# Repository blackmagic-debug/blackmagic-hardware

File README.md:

This project has now moved to [codeberg](https://codeberg.org/blackmagic-debug/blackmagic-hardware). Please file any issues and pull
requests there.

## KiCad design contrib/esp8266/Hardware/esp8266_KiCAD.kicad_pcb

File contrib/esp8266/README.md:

ESP8266 Clone
========================================

A little adapter board for connecting ESP-01 module as a debugger.

Repository Contents
-------------------

* **/Production** - Gerber files, drill files, BOM, CPL file
* **/Hardware** - KiCad PCB files, footprints library
* **/Documents** - Schematics pdf

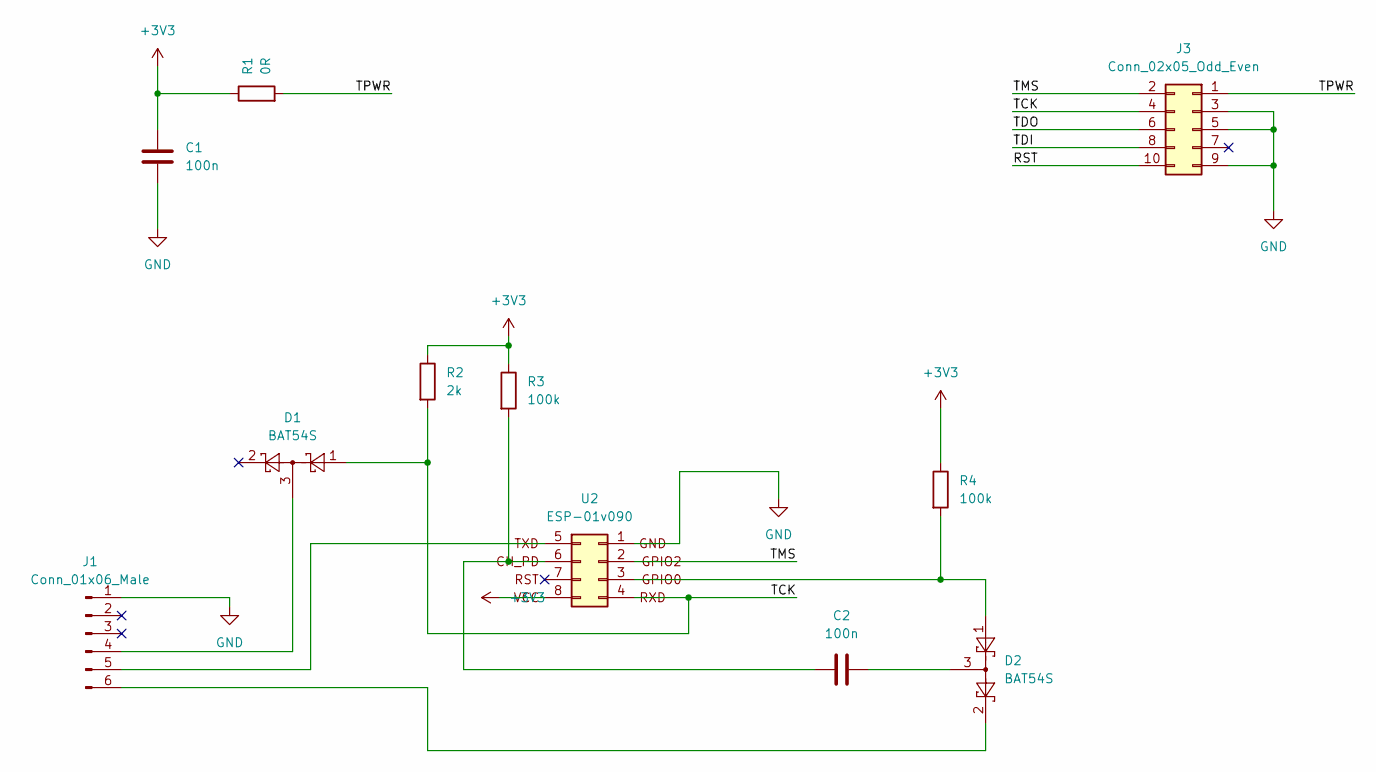
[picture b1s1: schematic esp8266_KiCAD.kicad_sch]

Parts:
C1, C2: 100n; C_0402_1005Metric; LCSC Number Part C1525
D1, D2: BAT54S; SOT-23; LCSC Number Part C727126
J1: Conn_01x06_Male; PinHeader_1x06_P2.54mm_Vertical
J3: Conn_02x05_Odd_Even; FTSH; LCSC Number Part C2935458
R1: 0R; R_0402_1005Metric; LCSC Number Part C17168
R2: 2k; R_0402_1005Metric; LCSC Number Part C4109
R3, R4: 100k; R_0402_1005Metric; LCSC Number Part C25741
U2: ESP-01v090; ESP-01S; LCSC Number Part C503582

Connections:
+3V3: C1.1, R1.1, R2.1, R3.1, R4.1, U2.8 (Pin_7)
/RST: J3.10
/TCK: D1.1, J3.4, R2.2, U2.4 (Pin_8)
/TDI: J3.8
/TDO: J3.6
/TMS: J3.2, U2.2 (Pin_4)
/TPWR: J3.1, R1.2
GND: C1.2, J1.1, J3.3, J3.5, J3.9, U2.1 (Pin_2)
unnamed: C2.1, R3.2, U2.6 (Pin_3)
unnamed: C2.2, D2.3
unnamed: D1.3, J1.4
unnamed: D2.1, R4.2, U2.3 (Pin_6)
unnamed: D2.2, J1.6
unnamed: J1.5, U2.5 (Pin_1)

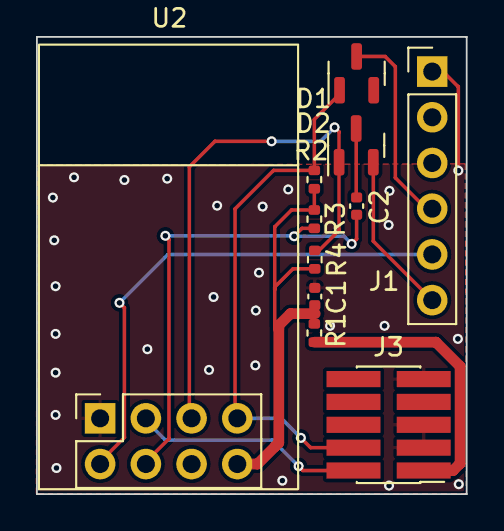
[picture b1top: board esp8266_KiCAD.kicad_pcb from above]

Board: 2 copper layers, 23.9 x 25.4 mm, 11 parts (0 on the bottom side), 11 nets.

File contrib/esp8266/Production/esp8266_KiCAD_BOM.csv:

"Source:","C:\Users\Sergio\Documents\EOS\esp8266\esp8266_KiCAD\esp8266_KiCAD\esp8266_KiCAD.kicad_sch"
"Date:","08/09/2022 10:14:48"
"Tool:","Eeschema (6.0.7)"
"Generator:","C:\Program Files\KiCad\6.0\bin\scripting\plugins/bom_csv_grouped_by_value.py"
"Component Count:","10"

"Individual Components:"

"Item","Qty","Reference(s)","Value","LibPart","Footprint","Datasheet","LCSC Number Part"
"","","C1","100n","Device:C","Capacitor_SMD:C_0402_1005Metric","~","C1525"
"","","C2","100n","Device:C","Capacitor_SMD:C_0402_1005Metric","~","C1525"
"","","D1","BAT54S","Diode:BAT54S","Package_TO_SOT_SMD:SOT-23","https://www.diodes.com/assets/Datasheets/ds11005.pdf","C727126"
"","","D2","BAT54S","Diode:BAT54S","Package_TO_SOT_SMD:SOT-23","https://www.diodes.com/assets/Datasheets/ds11005.pdf","C727126"
"","","J3","Conn_02x05_Odd_Even","Connector_Generic:Conn_02x05_Odd_Even","EOS:FTSH","~","C2935458"
"","","R1","0R","Device:R","Resistor_SMD:R_0402_1005Metric","~","C17168"
"","","R2","2k","Device:R","Resistor_SMD:R_0402_1005Metric","~","C4109"
"","","R3","100k","Device:R","Resistor_SMD:R_0402_1005Metric","~","C25741"
"","","R4","100k","Device:R","Resistor_SMD:R_0402_1005Metric","~","C25741"
"","","U2","ESP-01v090","Connector_Generic:Conn_02x04_Odd_Even","EOS:ESP-01S","~","C503582"

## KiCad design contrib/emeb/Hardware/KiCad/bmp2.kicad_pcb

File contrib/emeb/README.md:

Black Magic BMP2 Clone
========================================

Black Magic BMP2 is similar to Black Magic Mini but provides connections for several styles of JTAG connectors.

It is an easy-to-use board used for debugging embedded microcontrollers. It supports several targets from manufacturers such as STMicroelectronics, Atmel, Nordic Semiconductor, NXP, Texas Instruments, Freescale, Silicon Labs, Xilinx or Raspberry Pi.

GNU debugger
-------------------
The Black Magic GNU DeBugger (GDB) server features:
* Automatic target detection
* No need for target specific configuration scripts
* Easily scriptable
* Interface to the host computer does not require special drivers
* Full debugging functionality
* Works with Windows, Linux and Mac environments

Repository Contents
-------------------

* **/Production** - Gerber files, drill files, BOM, CPL file
* **/Hardware** - KiCad PCB files, footprints library
* **/Documents** - Schematics pdf

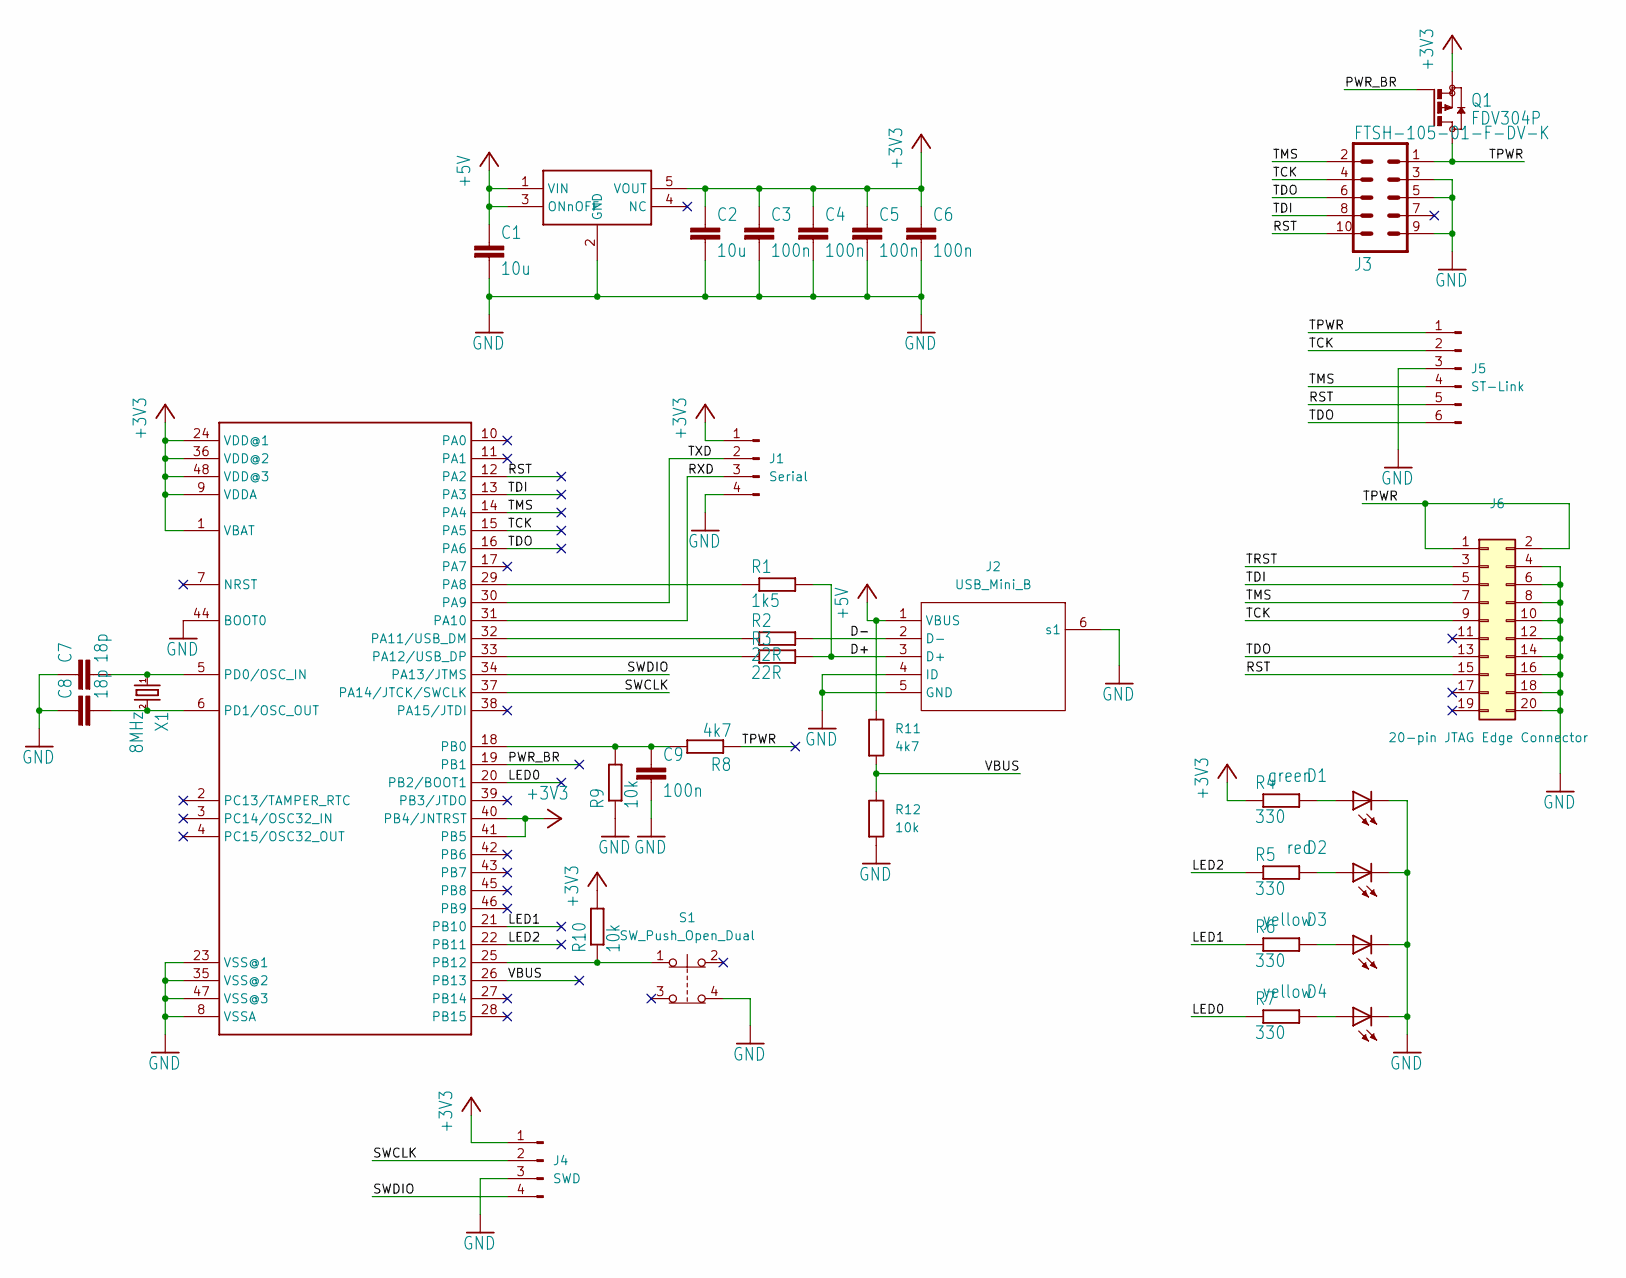
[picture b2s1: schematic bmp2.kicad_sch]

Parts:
C1, C2: 10u; C_0805_2012Metric; LCSC Number Part C17024
C3, C4, C5, C6, C9: 100n; C_0603_1608Metric; LCSC Number Part C1591
C7, C8: 18p; C_0603_1608Metric; LCSC Number Part C1647
D1: green; LED_0805_2012Metric; LCSC Number Part C434432
D2: red; LED_0805_2012Metric; LCSC Number Part C434431
D3, D4: yellow; LED_0805_2012Metric; LCSC Number Part C434436
J1: Serial; PinHeader_1x04_P2.54mm_Vertical
J2: USB_Mini_B; U-M-M5SS-W-2; LCSC Number Part C91144
J3: FTSH-105-01-F-DV-K; X1270WVS-2x05A-6TV01; LCSC Number Part C2962222
J4: SWD; PinHeader_1x04_P2.54mm_Vertical
J5: ST-Link; PinHeader_1x06_P2.54mm_Vertical
J6: 20-pin JTAG Edge Connector; 20-pin JTAG
Q1: FDV304P; SOT-23; LCSC Number Part C709971
R1: 1k5; R_0603_1608Metric; LCSC Number Part C22843
R2, R3: 22R; R_0603_1608Metric; LCSC Number Part C23345
R4, R5, R6, R7: 330; R_0603_1608Metric; LCSC Number Part C23138
R8, R11: 4k7; R_0603_1608Metric; LCSC Number Part C23162
R9, R10, R12: 10k; R_0603_1608Metric; LCSC Number Part C25804
S1: SW_Push_Open_Dual; UK-B0267-SP25Y; LCSC Number Part C493283
U1: MCP1802; SOT-23-5; LCSC Number Part C48292
U2: STM32F102CB; TQFP48; LCSC Number Part C8304
X1: 8MHz; 6I08000F20UCG; LCSC Number Part C251585

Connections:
+3V3: C2.1, C3.1, C4.1, C5.1, C6.1, J1.1, J4.1, Q1.2 (S), R4.1, R10.2, U1.5 (VOUT), U2.1 (VBAT), U2.9 (VDDA), U2.24 (VDD@1), U2.36 (VDD@2), U2.40 (PB4/JNTRST), U2.41 (PB5), U2.48 (VDD@3)
+5V: C1.1, J2.1 (VBUS), R11.1, U1.1 (VIN), U1.3 (ONnOFF)
/D+: J2.3 (D+), R1.2, R3.2
/D-: J2.2 (D-), R2.2
/LED0: R7.1, U2.20 (PB2/BOOT1)
/LED1: R6.1, U2.21 (PB10)
/LED2: R5.1, U2.22 (PB11)
/PWR_BR: Q1.1 (G), U2.19 (PB1)
/RST: J3.10, J5.5, J6.15, U2.12 (PA2)
/RXD: J1.3, U2.31 (PA10)
/SWCLK: J4.2, U2.37 (PA14/JTCK/SWCLK)
/SWDIO: J4.4, U2.34 (PA13/JTMS)
/TCK: J3.4, J5.2, J6.9, U2.15 (PA5)
/TDI: J3.8, J6.5, U2.13 (PA3)
/TDO: J3.6, J5.6, J6.13, U2.16 (PA6)
/TMS: J3.2, J5.4, J6.7, U2.14 (PA4)
/TPWR: J3.1, J5.1, J6.1, J6.2, Q1.3 (D), R8.1
/TRST: J6.3
/TXD: J1.2, U2.30 (PA9)
/VBUS: R11.2, R12.1, U2.26 (PB13)
GND: C1.2, C2.2, C3.2, C4.2, C5.2, C6.2, C7.1, C8.1, C9.2, D1.2 (C), D2.2 (C), D3.2 (C), D4.2 (C), J1.4, J2.4 (ID), J2.5 (GND), J2.6 (s1), J3.3, J3.5, J3.9, J4.3, J5.3, J6.4, J6.6, J6.8, J6.10, J6.12, J6.14, J6.16, J6.18, J6.20, R9.1, R12.2, S1.4, U1.2 (GND), U2.8 (VSSA), U2.23 (VSS@1), U2.35 (VSS@2), U2.44 (BOOT0), U2.47 (VSS@3)
unnamed: C7.2, U2.5 (PD0/OSC_IN), X1.1
unnamed: C8.2, U2.6 (PD1/OSC_OUT), X1.2
unnamed: C9.1, R8.2, R9.2, U2.18 (PB0)
unnamed: D1.1 (A), R4.2
unnamed: D2.1 (A), R5.2
unnamed: D3.1 (A), R6.2
unnamed: D4.1 (A), R7.2
unnamed: R1.1, U2.29 (PA8)
unnamed: R2.1, U2.32 (PA11/USB_DM)
unnamed: R3.1, U2.33 (PA12/USB_DP)
unnamed: R10.1, S1.1, U2.25 (PB12)

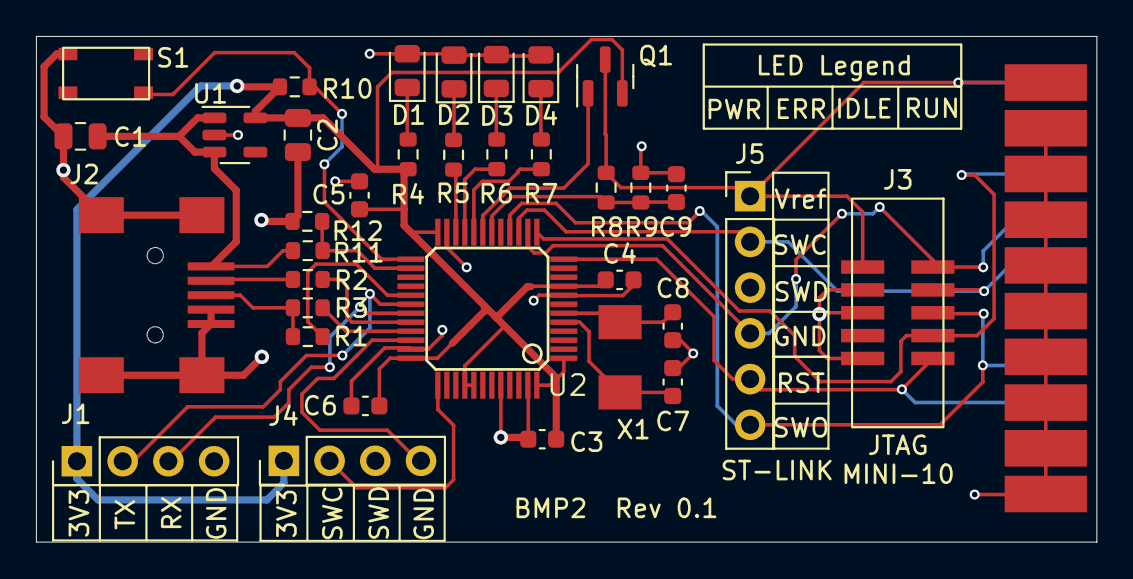
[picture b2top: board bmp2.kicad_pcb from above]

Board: 2 copper layers, 58.9 x 28.1 mm, 36 parts (0 on the bottom side), 31 nets.

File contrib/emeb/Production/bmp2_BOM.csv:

"Source:","C:\Users\Sergio\Documents\EOS\blackmagic-hardware-master\contrib\bmp2\bmp2_KiCAD\bmp2_KiCAD\bmp2.kicad_sch"
"Date:","01/09/2022 12:01:49"
"Tool:","Eeschema (6.0.7)"
"Generator:","C:\Program Files\KiCad\6.0\bin\scripting\plugins/bom_csv_grouped_by_value.py"
"Component Count:","32"

"Individual Components:"

"Item","Qty","Reference(s)","Value","LibPart","Footprint","Datasheet","LCSC Number Part"
"","","C1","10u","bmp_entropia-eagle-import:C-EUC0603","Capacitor_SMD:C_0805_2012Metric","","C17024"
"","","C2","10u","bmp_entropia-eagle-import:C-EUC0603","Capacitor_SMD:C_0805_2012Metric","","C17024"
"","","C3","100n","bmp_entropia-eagle-import:C-EUC0603","Capacitor_SMD:C_0603_1608Metric","","C1591"
"","","C4","100n","bmp_entropia-eagle-import:C-EUC0603","Capacitor_SMD:C_0603_1608Metric","","C1591"
"","","C5","100n","bmp_entropia-eagle-import:C-EUC0603","Capacitor_SMD:C_0603_1608Metric","","C1591"
"","","C6","100n","bmp_entropia-eagle-import:C-EUC0603","Capacitor_SMD:C_0603_1608Metric","","C1591"
"","","C7","18p","bmp_entropia-eagle-import:C-EUC0603","Capacitor_SMD:C_0603_1608Metric","","C1647"
"","","C8","18p","bmp_entropia-eagle-import:C-EUC0603","Capacitor_SMD:C_0603_1608Metric","","C1647"
"","","C9","100n","bmp_entropia-eagle-import:C-EUC0603","Capacitor_SMD:C_0603_1608Metric","","C1591"
"","","D1","green",":LEDCHIPLED_0603_1","LED_SMD:LED_0805_2012Metric","","C434432"
"","","D2","red",":LEDCHIPLED_0603_2","LED_SMD:LED_0805_2012Metric","","C434431"
"","","D3","yellow",":LEDCHIPLED_0603_3","LED_SMD:LED_0805_2012Metric","","C434436"
"","","D4","yellow","bmp_entropia-eagle-import:LEDCHIPLED_0603","LED_SMD:LED_0805_2012Metric","","C434436"
"","","J2","USB_Mini_B","BMP2:USB_Mini_B","EOS:U-M-M5SS-W-2","","C91144"
"","","J3","FTSH-105-01-F-DV-K","bmp_entropia-eagle-import:MA05-2","EOS:X1270WVS-2x05A-6TV01","","C2962222"
"","","Q1","FDV304P","bmp_entropia-eagle-import:BSS84","Package_TO_SOT_SMD:SOT-23","","C709971"
"","","R1","1k5","bmp_entropia-eagle-import:R-EU_R0603","Resistor_SMD:R_0603_1608Metric","","C22843"
"","","R2","22R","bmp_entropia-eagle-import:R-EU_R0603","Resistor_SMD:R_0603_1608Metric","","C23345"
"","","R3","22R","bmp_entropia-eagle-import:R-EU_R0603","Resistor_SMD:R_0603_1608Metric","","C23345"
"","","R4","330","bmp_entropia-eagle-import:R-EU_R0603","Resistor_SMD:R_0603_1608Metric","","C23138"
"","","R5","330","bmp_entropia-eagle-import:R-EU_R0603","Resistor_SMD:R_0603_1608Metric","","C23138"
"","","R6","330","bmp_entropia-eagle-import:R-EU_R0603","Resistor_SMD:R_0603_1608Metric","","C23138"
"","","R7","330","bmp_entropia-eagle-import:R-EU_R0603","Resistor_SMD:R_0603_1608Metric","","C23138"
"","","R8","4k7","bmp_entropia-eagle-import:R-EU_R0603","Resistor_SMD:R_0603_1608Metric","","C23162"
"","","R9","10k","bmp_entropia-eagle-import:R-EU_R0603","Resistor_SMD:R_0603_1608Metric","","C25804"
"","","R10","10k","bmp_entropia-eagle-import:R-EU_R0603","Resistor_SMD:R_0603_1608Metric","","C25804"
"","","R11","4k7","Device:R","Resistor_SMD:R_0603_1608Metric","~","C23162"
"","","R12","10k","Device:R","Resistor_SMD:R_0603_1608Metric","~","C25804"
"","","S1","SW_Push_Open_Dual","Switch:SW_Push_Open_Dual","EOS:UK-B0267-SP25Y","~","C493283"
"","","U1","MCP1802","bmp_entropia-eagle-import:TLV700DCK","Package_TO_SOT_SMD:SOT-23-5","","C48292"
"","","U2","STM32F102CB","bmp_entropia-eagle-import:STM32F_48PIN","bmp_entropia:TQFP48","","C8304"
"","","X1","8MHz","bmp_entropia-eagle-import:CRYSTALHC49S","EOS:6I08000F20UCG","","C251585"

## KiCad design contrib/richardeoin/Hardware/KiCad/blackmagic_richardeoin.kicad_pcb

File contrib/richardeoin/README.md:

Black Magic Richardeoin Clone
========================================

Black Magic Richardeoin is version of Black Magic Mini with some differences such as the useage of 0603 components or a BOOT0 button.

It is an easy-to-use board used for debugging embedded microcontrollers. It supports several targets from manufacturers such as STMicroelectronics, Atmel, Nordic Semiconductor, NXP, Texas Instruments, Freescale, Silicon Labs, Xilinx or Raspberry Pi.

GNU debugger
-------------------
The Black Magic GNU DeBugger (GDB) server features:
* Automatic target detection
* No need for target specific configuration scripts
* Easily scriptable
* Interface to the host computer does not require special drivers
* Full debugging functionality
* Works with Windows, Linux and Mac environments

Repository Contents
-------------------

* **/Production** - Gerber files, drill files, BOM, CPL file
* **/Hardware** - KiCad PCB files, footprints library
* **/Documents** - Schematics pdf

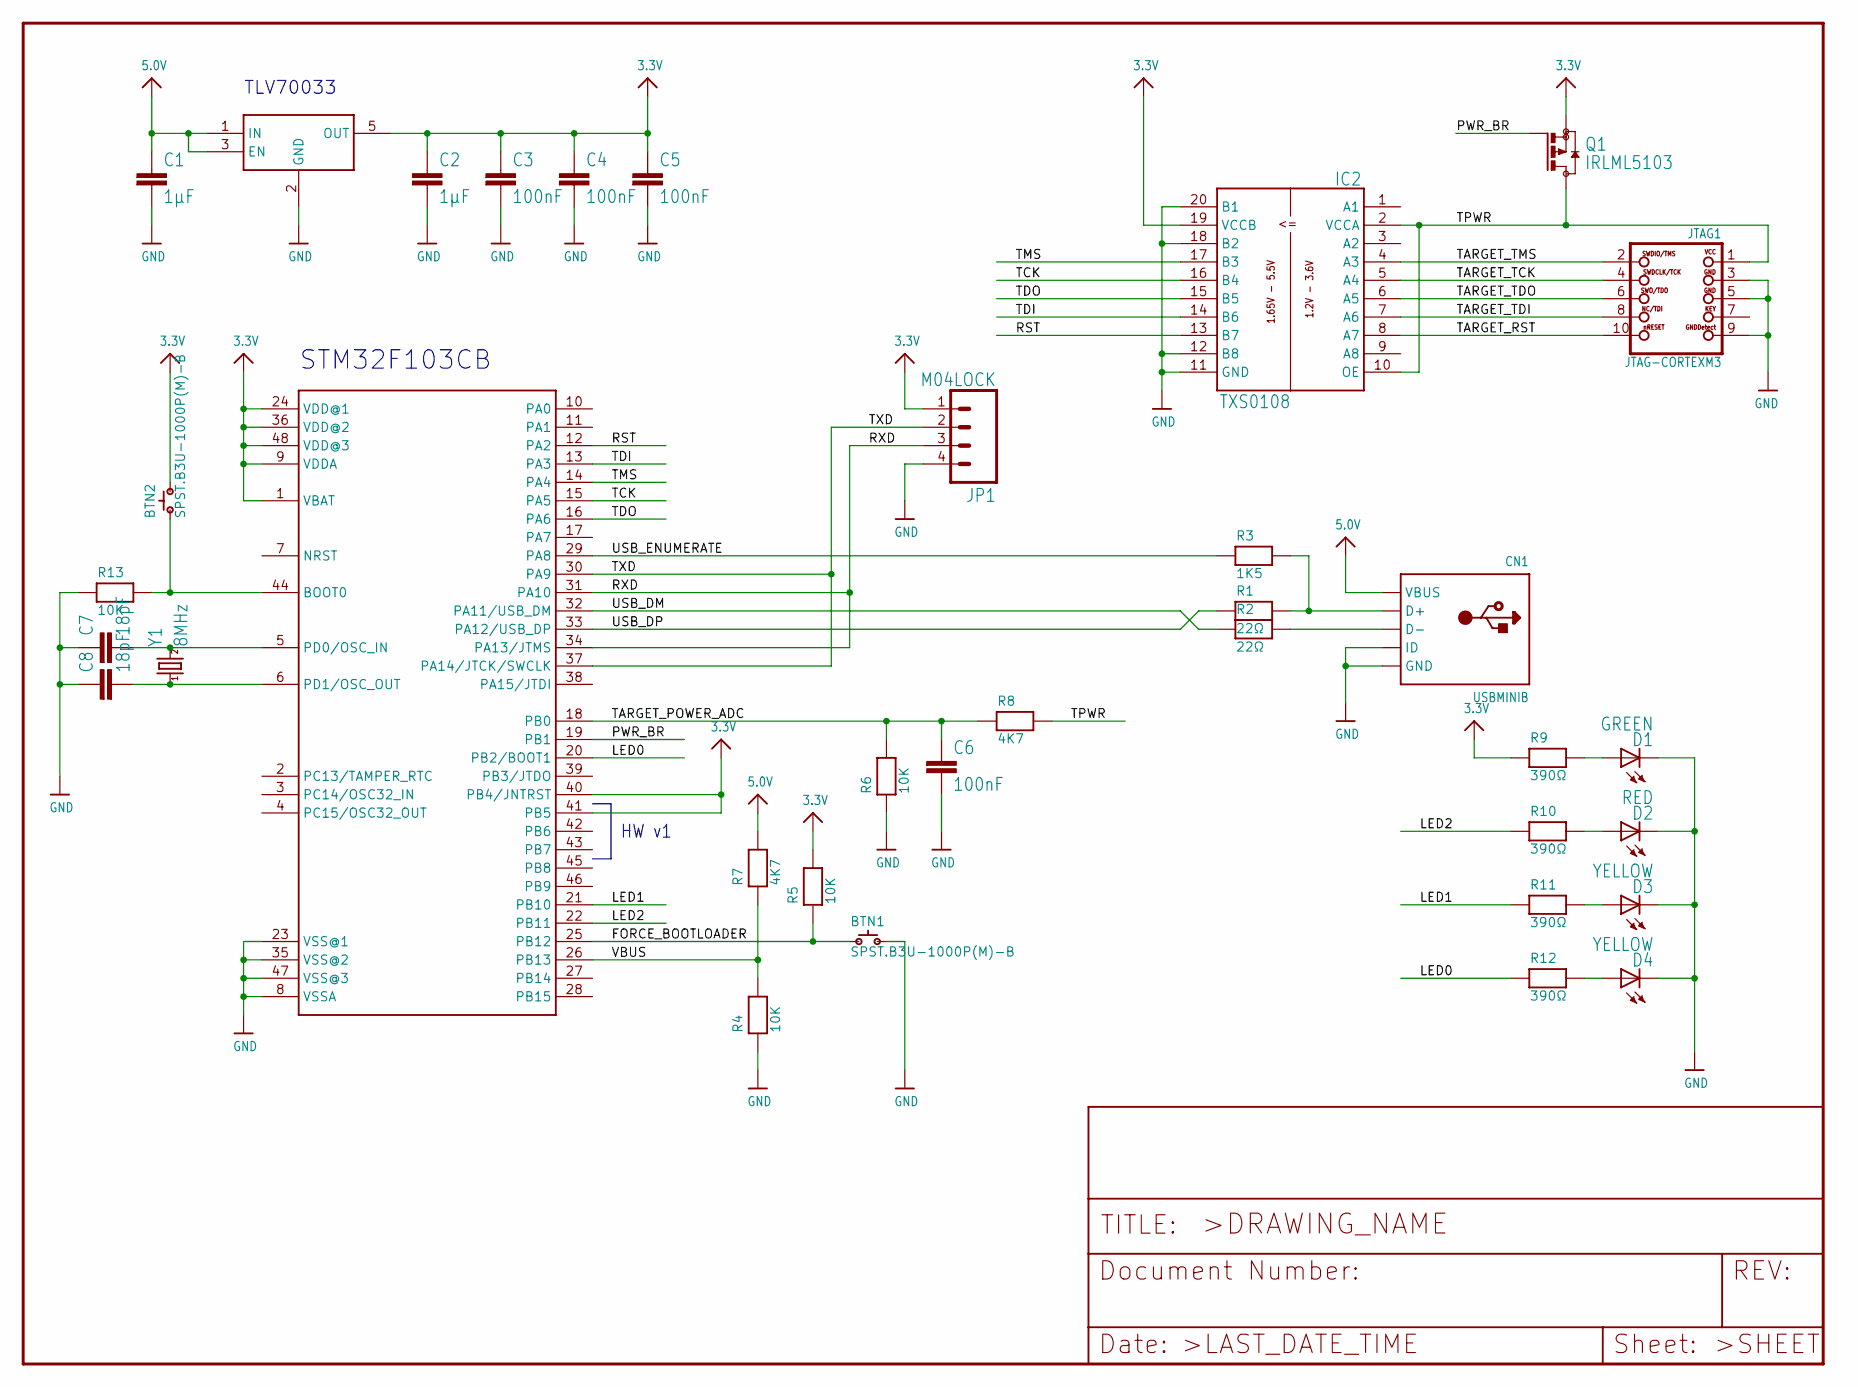
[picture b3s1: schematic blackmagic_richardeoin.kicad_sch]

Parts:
BTN1, BTN2: SPST.B3U-1000P(M)-B; B3U-1000P(M)-B; LCSC Number Part C231329
C1, C2: 1µF; C0603K; LCSC Number Part C1592
C3, C4, C5, C6: 100nF; C0603K; LCSC Number Part C1591
C7, C8: 18pF; C0603K; LCSC Number Part C1647
CN1: USBMINIB; USB-MINIB; LCSC Number Part C69074
D1: GREEN; CHIPLED_0603; LCSC Number Part C434420
D2: RED; CHIPLED_0603; LCSC Number Part C375444
D3, D4: YELLOW; CHIPLED_0603; LCSC Number Part C89811
IC1: STM32F_48PIN; TQFP48; LCSC Number Part C8304
IC2: TXS0108; TSSOP20; LCSC Number Part C17206
IC3: TLV70033DCK; SC70-5L; LCSC Number Part C47945
JP1: M04LOCK; 1X04_LOCK
JTAG1: JTAG-CORTEXM3; 2X05_1.27MM_SMT; LCSC Number Part C2962222
Q1: IRLML5103; SOT23; LCSC Number Part C2591
R1, R2: 22Ω; 0603-MINI; LCSC Number Part C96423
R3: 1K5; 0603-MINI; LCSC Number Part C22843
R4, R5, R6, R13: 10K; 0603-MINI; LCSC Number Part C25804
R7, R8: 4K7; 0603-MINI; LCSC Number Part C23162
R9, R10, R11, R12: 390Ω; 0603-MINI; LCSC Number Part C23151
Y1: 8MHz; CRYSTAL-SMD-5X3; LCSC Number Part C133333

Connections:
3.3V: BTN2.2, C2.1, C3.1, C4.1, C5.1, IC1.1 (VBAT), IC1.9 (VDDA), IC1.24 (VDD@1), IC1.36 (VDD@2), IC1.40 (PB4/JNTRST), IC1.41 (PB5), IC1.48 (VDD@3), IC2.19 (VCCB), IC3.5 (OUT), JP1.1, Q1.2 (S), R5.2, R9.1
5.0V: C1.1, CN1.VBUS, IC3.1 (IN), IC3.3 (EN), R7.2
BOOT0: BTN2.1, IC1.44 (BOOT0), R13.2
D+: CN1.D+, R1.2, R3.2
D-: CN1.D-, R2.2
FORCE_BOOTLOADER: BTN1.1, IC1.25 (PB12), R5.1
GND: BTN1.2, C1.2, C2.2, C3.2, C4.2, C5.2, C6.2, C7.1, C8.1, CN1.GND, CN1.ID, D1.C, D2.C, D3.C, D4.C, IC1.8 (VSSA), IC1.23 (VSS@1), IC1.35 (VSS@2), IC1.47 (VSS@3), IC2.11 (GND), IC2.12 (B8), IC2.18 (B2), IC2.20 (B1), IC3.2 (GND), JP1.4, JTAG1.3, JTAG1.5, JTAG1.9, R4.1, R6.1, R13.1
LED0: IC1.20 (PB2/BOOT1), R12.1
LED1: IC1.21 (PB10), R11.1
LED2: IC1.22 (PB11), R10.1
LPC_XTAL2: C8.2, IC1.6 (PD1/OSC_OUT), Y1.1
unnamed: D2.A, R10.2
unnamed: D1.A, R9.2
unnamed: D3.A, R11.2
unnamed: D4.A, R12.2
OSC_IN: C7.2, IC1.5 (PD0/OSC_IN), Y1.3 (2)
PWR_BR: IC1.19 (PB1), Q1.1 (G)
RST: IC1.12 (PA2), IC2.13 (B7)
RXD: IC1.31 (PA10), IC1.34 (PA13/JTMS), JP1.3
TARGET_POWER_ADC: C6.1, IC1.18 (PB0), R6.2, R8.1
TARGET_RST: IC2.8 (A7), JTAG1.10
TARGET_TCK: IC2.5 (A4), JTAG1.4
TARGET_TDI: IC2.7 (A6), JTAG1.8
TARGET_TDO: IC2.6 (A5), JTAG1.6
TARGET_TMS: IC2.4 (A3), JTAG1.2
TCK: IC1.15 (PA5), IC2.16 (B4)
TDI: IC1.13 (PA3), IC2.14 (B6)
TDO: IC1.16 (PA6), IC2.15 (B5)
TMS: IC1.14 (PA4), IC2.17 (B3)
TPWR: IC2.2 (VCCA), IC2.10 (OE), JTAG1.1, Q1.3 (D), R8.2
TXD: IC1.30 (PA9), IC1.37 (PA14/JTCK/SWCLK), JP1.2
USB_DM: IC1.32 (PA11/USB_DM), R2.1
USB_DP: IC1.33 (PA12/USB_DP), R1.1
USB_ENUMERATE: IC1.29 (PA8), R3.1
VBUS: IC1.26 (PB13), R4.2, R7.1

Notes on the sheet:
TLV70033
HW v1
STM32F103CB

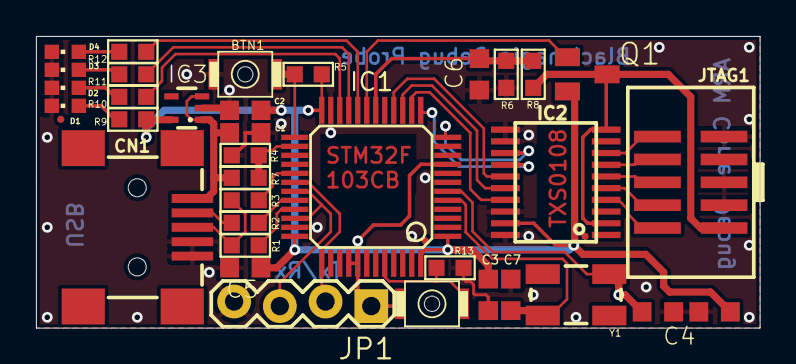
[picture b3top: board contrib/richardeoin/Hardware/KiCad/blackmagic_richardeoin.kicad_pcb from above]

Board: 2 copper layers, 40.2 x 16.2 mm, 35 parts (0 on the bottom side), 35 nets.

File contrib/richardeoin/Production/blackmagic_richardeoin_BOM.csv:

"Source:","C:\Users\Sergio\Documents\EOS\blackmagic-hardware-master\contrib\richardeoin\richardeoin_KiCAD\blackmagic_richardeoin.kicad_sch"
"Date:","30/08/2022 17:34:46"
"Tool:","Eeschema (6.0.7)"
"Generator:","C:\Program Files\KiCad\6.0\bin\scripting\plugins/bom_csv_grouped_by_value.py"
"Component Count:","34"

"Individual Components:"

"Item","Qty","Reference(s)","Value","LibPart","Footprint","Datasheet","LCSC Number Part"
"","","BTN1","SPST.B3U-1000P(M)-B","blackmagic_richardeoin-eagle-import:SPST.B3U-1000P(M)-B","blackmagic_richardeoin:B3U-1000P(M)-B","","C231329"
"","","BTN2","SPST.B3U-1000P(M)-B","blackmagic_richardeoin-eagle-import:SPST.B3U-1000P(M)-B","blackmagic_richardeoin:B3U-1000P(M)-B","","C231329"
"","","C1","1µF","blackmagic_richardeoin-eagle-import:C-EUC0603K","blackmagic_richardeoin:C0603K","","C1592"
"","","C2","1µF","blackmagic_richardeoin-eagle-import:C-EUC0603K","blackmagic_richardeoin:C0603K","","C1592"
"","","C3","100nF","blackmagic_richardeoin-eagle-import:C-EUC0603K","blackmagic_richardeoin:C0603K","","C1591"
"","","C4","100nF","blackmagic_richardeoin-eagle-import:C-EUC0603K","blackmagic_richardeoin:C0603K","","C1591"
"","","C5","100nF","blackmagic_richardeoin-eagle-import:C-EUC0603K","blackmagic_richardeoin:C0603K","","C1591"
"","","C6","100nF","blackmagic_richardeoin-eagle-import:C-EUC0603K","blackmagic_richardeoin:C0603K","","C1591"
"","","C7","18pF","blackmagic_richardeoin-eagle-import:C-EUC0603K","blackmagic_richardeoin:C0603K","","C1647"
"","","C8","18pF","blackmagic_richardeoin-eagle-import:C-EUC0603K","blackmagic_richardeoin:C0603K","","C1647"
"","","CN1","USBMINIB","blackmagic_richardeoin-eagle-import:USBMINIB","blackmagic_richardeoin:USB-MINIB","","C69074"
"","","D1","GREEN","blackmagic_richardeoin-eagle-import:LEDCHIPLED_0603","blackmagic_richardeoin:CHIPLED_0603","","C434420"
"","","D2","RED","blackmagic_richardeoin-eagle-import:LEDCHIPLED_0603","blackmagic_richardeoin:CHIPLED_0603","","C375444"
"","","D3","YELLOW","blackmagic_richardeoin-eagle-import:LEDCHIPLED_0603","blackmagic_richardeoin:CHIPLED_0603","","C89811"
"","","D4","YELLOW","blackmagic_richardeoin-eagle-import:LEDCHIPLED_0603","blackmagic_richardeoin:CHIPLED_0603","","C89811"
"","","IC1","STM32F_48PIN","blackmagic_richardeoin-eagle-import:STM32F_48PIN","blackmagic_richardeoin:TQFP48","","C8304"
"","","IC2","TXS0108","blackmagic_richardeoin-eagle-import:TX0108PWR","blackmagic_richardeoin:TSSOP20","","C17206"
"","","IC3","TLV70033DCK","blackmagic_richardeoin-eagle-import:TLV700DCK","blackmagic_richardeoin:SC70-5L","","C47945"
"","","JTAG1","JTAG-CORTEXM3","blackmagic_richardeoin-eagle-import:JTAG-CORTEXM3","blackmagic_richardeoin:2X05_1.27MM_SMT","","C2962222"
"","","Q1","IRLML5103","blackmagic_richardeoin-eagle-import:BSS84","blackmagic_richardeoin:SOT23","","C2591"
"","","R1","22Ω","blackmagic_richardeoin-eagle-import:RESISTOR0603MINI","blackmagic_richardeoin:0603-MINI","","C96423"
"","","R2","22Ω","blackmagic_richardeoin-eagle-import:RESISTOR0603MINI","blackmagic_richardeoin:0603-MINI","","C96423"
"","","R3","1K5","blackmagic_richardeoin-eagle-import:RESISTOR0603MINI","blackmagic_richardeoin:0603-MINI","","C22843"
"","","R4","10K","blackmagic_richardeoin-eagle-import:RESISTOR0603MINI","blackmagic_richardeoin:0603-MINI","","C25804"
"","","R5","10K","blackmagic_richardeoin-eagle-import:RESISTOR0603MINI","blackmagic_richardeoin:0603-MINI","","C25804"
"","","R6","10K","blackmagic_richardeoin-eagle-import:RESISTOR0603MINI","blackmagic_richardeoin:0603-MINI","","C25804"
"","","R7","4K7","blackmagic_richardeoin-eagle-import:RESISTOR0603MINI","blackmagic_richardeoin:0603-MINI","","C23162"
"","","R8","4K7","blackmagic_richardeoin-eagle-import:RESISTOR0603MINI","blackmagic_richardeoin:0603-MINI","","C23162"
"","","R9","390Ω","blackmagic_richardeoin-eagle-import:RESISTOR0603MINI","blackmagic_richardeoin:0603-MINI","","C23151"
"","","R10","390Ω","blackmagic_richardeoin-eagle-import:RESISTOR0603MINI","blackmagic_richardeoin:0603-MINI","","C23151"
"","","R11","390Ω","blackmagic_richardeoin-eagle-import:RESISTOR0603MINI","blackmagic_richardeoin:0603-MINI","","C23151"
"","","R12","390Ω","blackmagic_richardeoin-eagle-import:RESISTOR0603MINI","blackmagic_richardeoin:0603-MINI","","C23151"
"","","R13","10K","blackmagic_richardeoin-eagle-import:RESISTOR0603MINI","blackmagic_richardeoin:0603-MINI","","C25804"
"","","Y1","8MHz","blackmagic_richardeoin-eagle-import:CRYSTAL5X3","blackmagic_richardeoin:CRYSTAL-SMD-5X3","","C133333"

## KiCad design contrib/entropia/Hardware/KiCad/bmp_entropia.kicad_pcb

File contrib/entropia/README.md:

Black Magic Entropia Clone
========================================

Black Magic Entropia is similar to Black Magic Mini but only uses 0603 components and standard connectors.

It is an easy-to-use board used for debugging embedded microcontrollers. It supports several targets from manufacturers such as STMicroelectronics, Atmel, Nordic Semiconductor, NXP, Texas Instruments, Freescale, Silicon Labs, Xilinx or Raspberry Pi.

GNU debugger
-------------------
The Black Magic GNU DeBugger (GDB) server features:
* Automatic target detection
* No need for target specific configuration scripts
* Easily scriptable
* Interface to the host computer does not require special drivers
* Full debugging functionality
* Works with Windows, Linux and Mac environments

Repository Contents
-------------------

* **/Production** - Gerber files, drill files, BOM, CPL file
* **/Hardware** - KiCad PCB files, footprints library
* **/Documents** - Schematics pdf

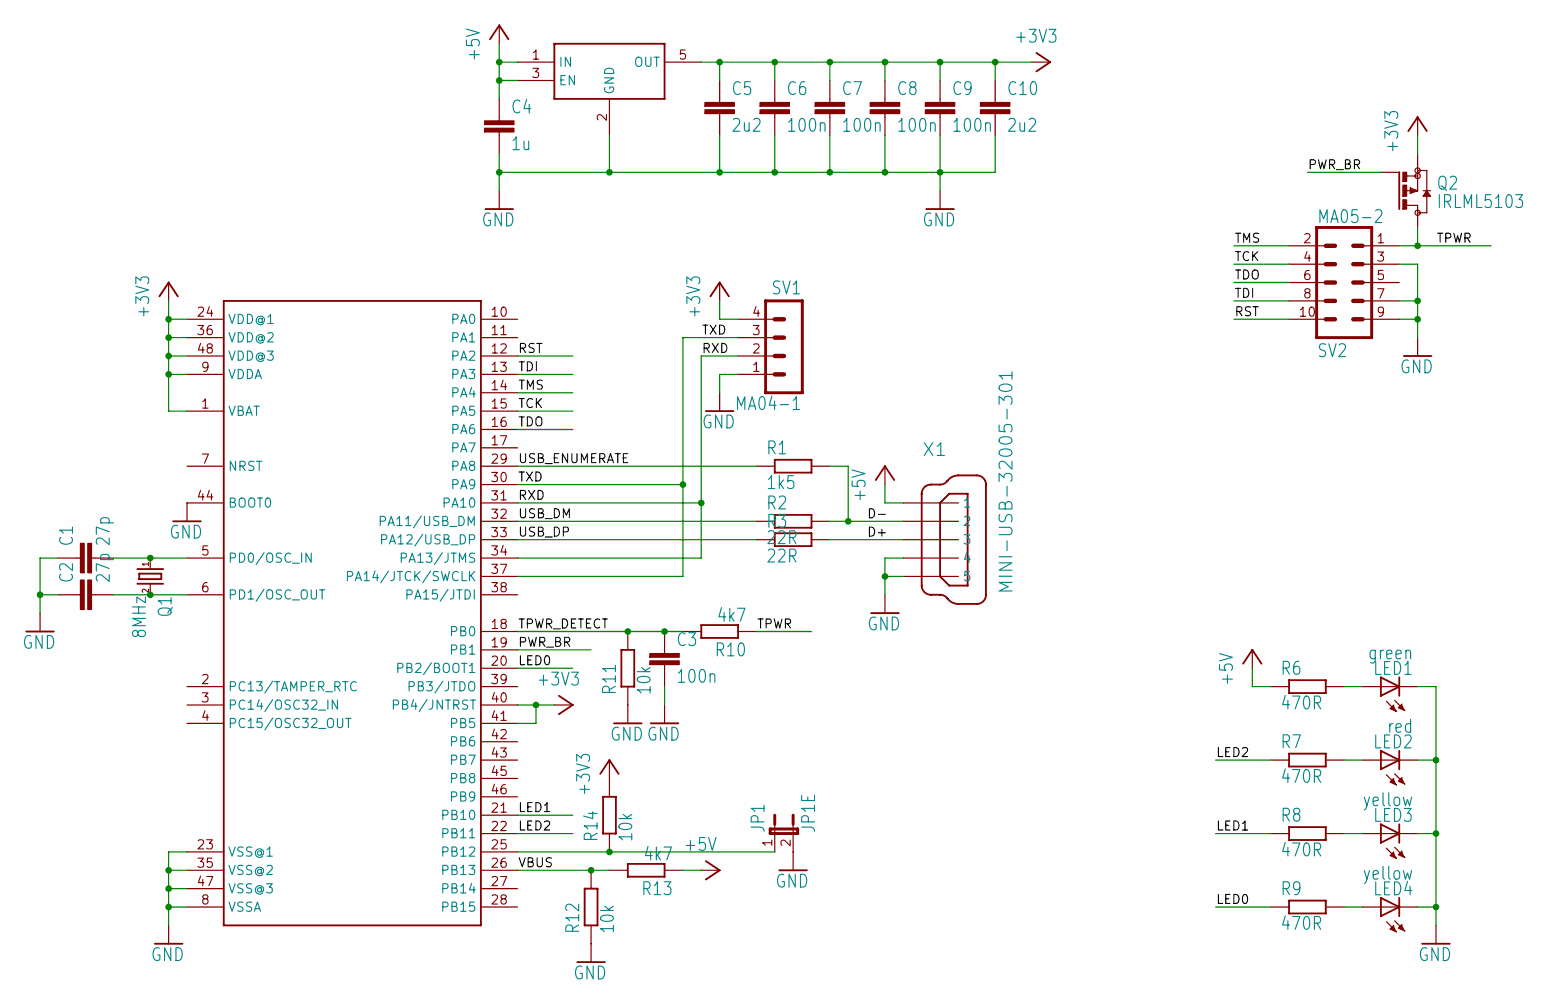
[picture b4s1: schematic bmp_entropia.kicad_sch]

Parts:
C1, C2: 27p; LCSC Number Part C1656
C3, C6, C7, C8, C9: 100n; LCSC Number Part C1591
C4: 1u; LCSC Number Part C1592
C5, C10: 2u2; LCSC Number Part C71000
JP1: JP1E
LED1: green; LCSC Number Part C434420
LED2: red; LCSC Number Part C375444
LED3, LED4: yellow; LCSC Number Part C89811
Q1: 8MHz; LCSC Number Part C258976
Q2: IRLML5103; LCSC Number Part C2591
R1: 1k5; LCSC Number Part C22843
R2, R3: 22R; LCSC Number Part C96423
R6, R7, R8, R9: 470R; LCSC Number Part C23179
R10, R13: 4k7; LCSC Number Part C23162
R11, R12, R14: 10k; LCSC Number Part C25804
SV1: MA04-1
SV2: MA05-2
U$1: STM32F_48PIN; LCSC Number Part C8304
U$2: TLV70033DCK; LCSC Number Part C47945
X1: MINI-USB-32005-301; LCSC Number Part C69074

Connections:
+3V3: C5.1, C6.1, C7.1, C8.1, C9.1, C10.1, Q2.2 (S), R14.2, SV1.4, U$1.1 (VBAT), U$1.9 (VDDA), U$1.24 (VDD@1), U$1.36 (VDD@2), U$1.40 (PB4/JNTRST), U$1.41 (PB5), U$1.48 (VDD@3), U$2.5 (OUT)
+5V: C4.1, R6.1, R13.1, U$2.1 (IN), U$2.3 (EN), X1.1
D+: R3.2, X1.3
D-: R1.2, R2.2, X1.2
GND: C1.1, C2.1, C3.2, C4.2, C5.2, C6.2, C7.2, C8.2, C9.2, C10.2, JP1.2, LED1.C, LED2.C, LED3.C, LED4.C, R11.1, R12.1, SV1.1, SV2.3, SV2.7, SV2.9, U$1.8 (VSSA), U$1.23 (VSS@1), U$1.35 (VSS@2), U$1.44 (BOOT0), U$1.47 (VSS@3), U$2.2 (GND), X1.4, X1.5
LED0: R9.1, U$1.20 (PB2/BOOT1)
LED1: R8.1, U$1.21 (PB10)
LED2: R7.1, U$1.22 (PB11)
LED_G: LED1.A, R6.2
LED_R: LED2.A, R7.2
LED_Y0: LED4.A, R9.2
LED_Y1: LED3.A, R8.2
OSC_IN: C1.2, Q1.1, U$1.5 (PD0/OSC_IN)
OSC_OUT: C2.2, Q1.2, U$1.6 (PD1/OSC_OUT)
PWR_BR: Q2.1 (G), U$1.19 (PB1)
RST: SV2.10, U$1.12 (PA2)
RXD: SV1.2, U$1.31 (PA10), U$1.34 (PA13/JTMS)
TASTER: JP1.1, R14.1, U$1.25 (PB12)
TCK: SV2.4, U$1.15 (PA5)
TDI: SV2.8, U$1.13 (PA3)
TDO: SV2.6, U$1.16 (PA6)
TMS: SV2.2, U$1.14 (PA4)
TPWR: Q2.3 (D), R10.1, SV2.1
TPWR_DETECT: C3.1, R10.2, R11.2, U$1.18 (PB0)
TXD: SV1.3, U$1.30 (PA9), U$1.37 (PA14/JTCK/SWCLK)
USB_DM: R2.1, U$1.32 (PA11/USB_DM)
USB_DP: R3.1, U$1.33 (PA12/USB_DP)
USB_ENUMERATE: R1.1, U$1.29 (PA8)
VBUS: R12.2, R13.2, U$1.26 (PB13)

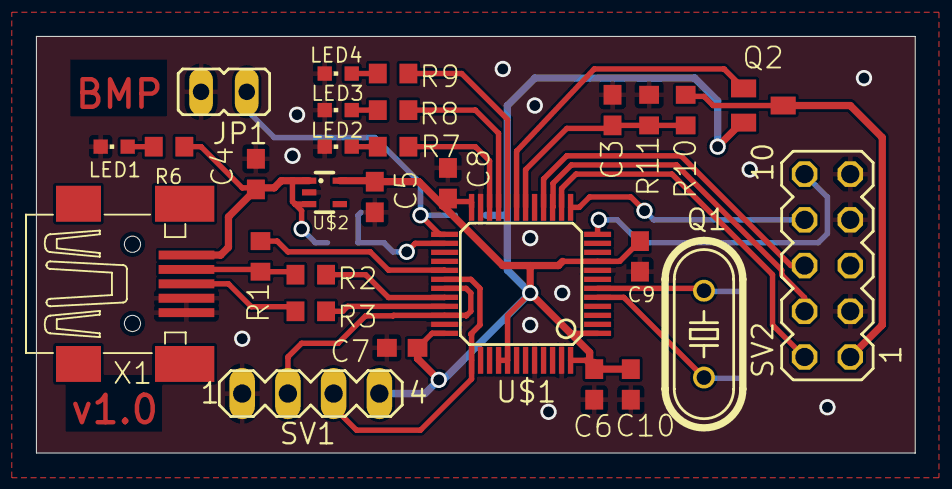
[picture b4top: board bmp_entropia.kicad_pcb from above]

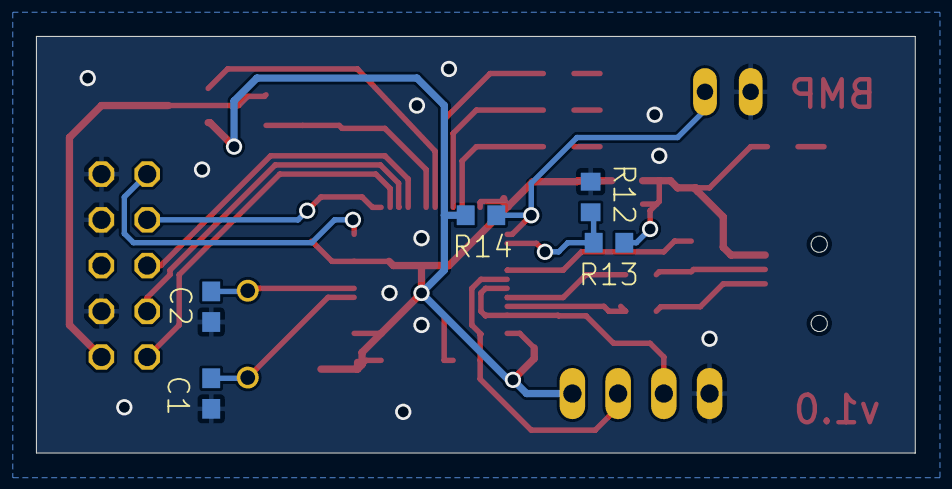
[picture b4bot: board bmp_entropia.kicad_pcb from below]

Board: 2 copper layers, 48.8 x 23.1 mm, 34 parts (5 on the bottom side), 29 nets.

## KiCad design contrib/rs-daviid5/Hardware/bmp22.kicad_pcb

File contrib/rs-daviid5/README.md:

Black Magic BMP22 Clone
========================================

BMP22 is a version of the Black Magic Mini.

It is an easy-to-use board used for debugging embedded microcontrollers. It supports several targets from manufacturers such as STMicroelectronics, Atmel, Nordic Semiconductor, NXP, Texas Instruments, Freescale, Silicon Labs, Xilinx or Raspberry Pi.

GNU debugger
-------------------
The Black Magic GNU DeBugger (GDB) server features:
* Automatic target detection
* No need for target specific configuration scripts
* Easily scriptable
* Interface to the host computer does not require special drivers
* Full debugging functionality
* Works with Windows, Linux and Mac environments

Repository Contents
-------------------

* **/Production** - Gerber files, drill files, BOM, CPL file
* **/Hardware** - KiCad PCB files, footprints library
* **/Documents** - Schematics pdf

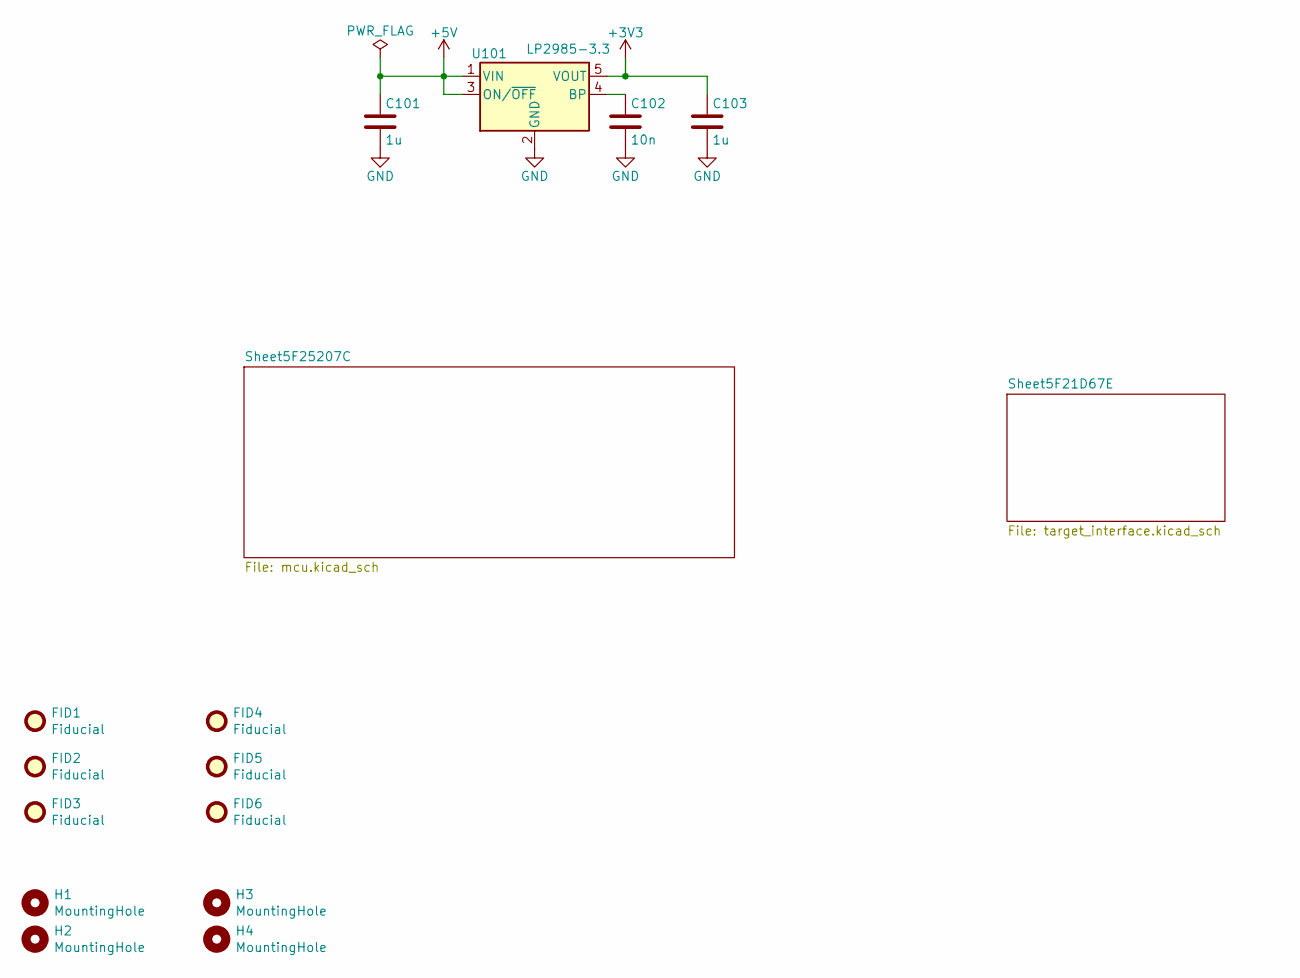
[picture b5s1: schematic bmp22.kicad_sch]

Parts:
C101, C103: 1u; C_0603_1608Metric; LCSC Number Part C15849
C102: 10n; C_0603_1608Metric; LCSC Number Part C57112
FID1, FID2, FID3, FID4, FID5, FID6: Fiducial; Fiducial_1mm_Mask2mm
H1, H2, H3, H4: MountingHole; MountingHole_2.7mm_M2.5_DIN965
U101: LP2985-3.3; SOT-23-5; LCSC Number Part C95414

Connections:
+3V3: C103.1, U101.5 (VOUT); also elsewhere on the board
+5V: C101.1, U101.1 (VIN), U101.3 (ON/~OFF); also elsewhere on the board
GND: C101.2, C102.2, C103.2, U101.2 (GND); also elsewhere on the board
unnamed: C102.1, U101.4 (BP)
